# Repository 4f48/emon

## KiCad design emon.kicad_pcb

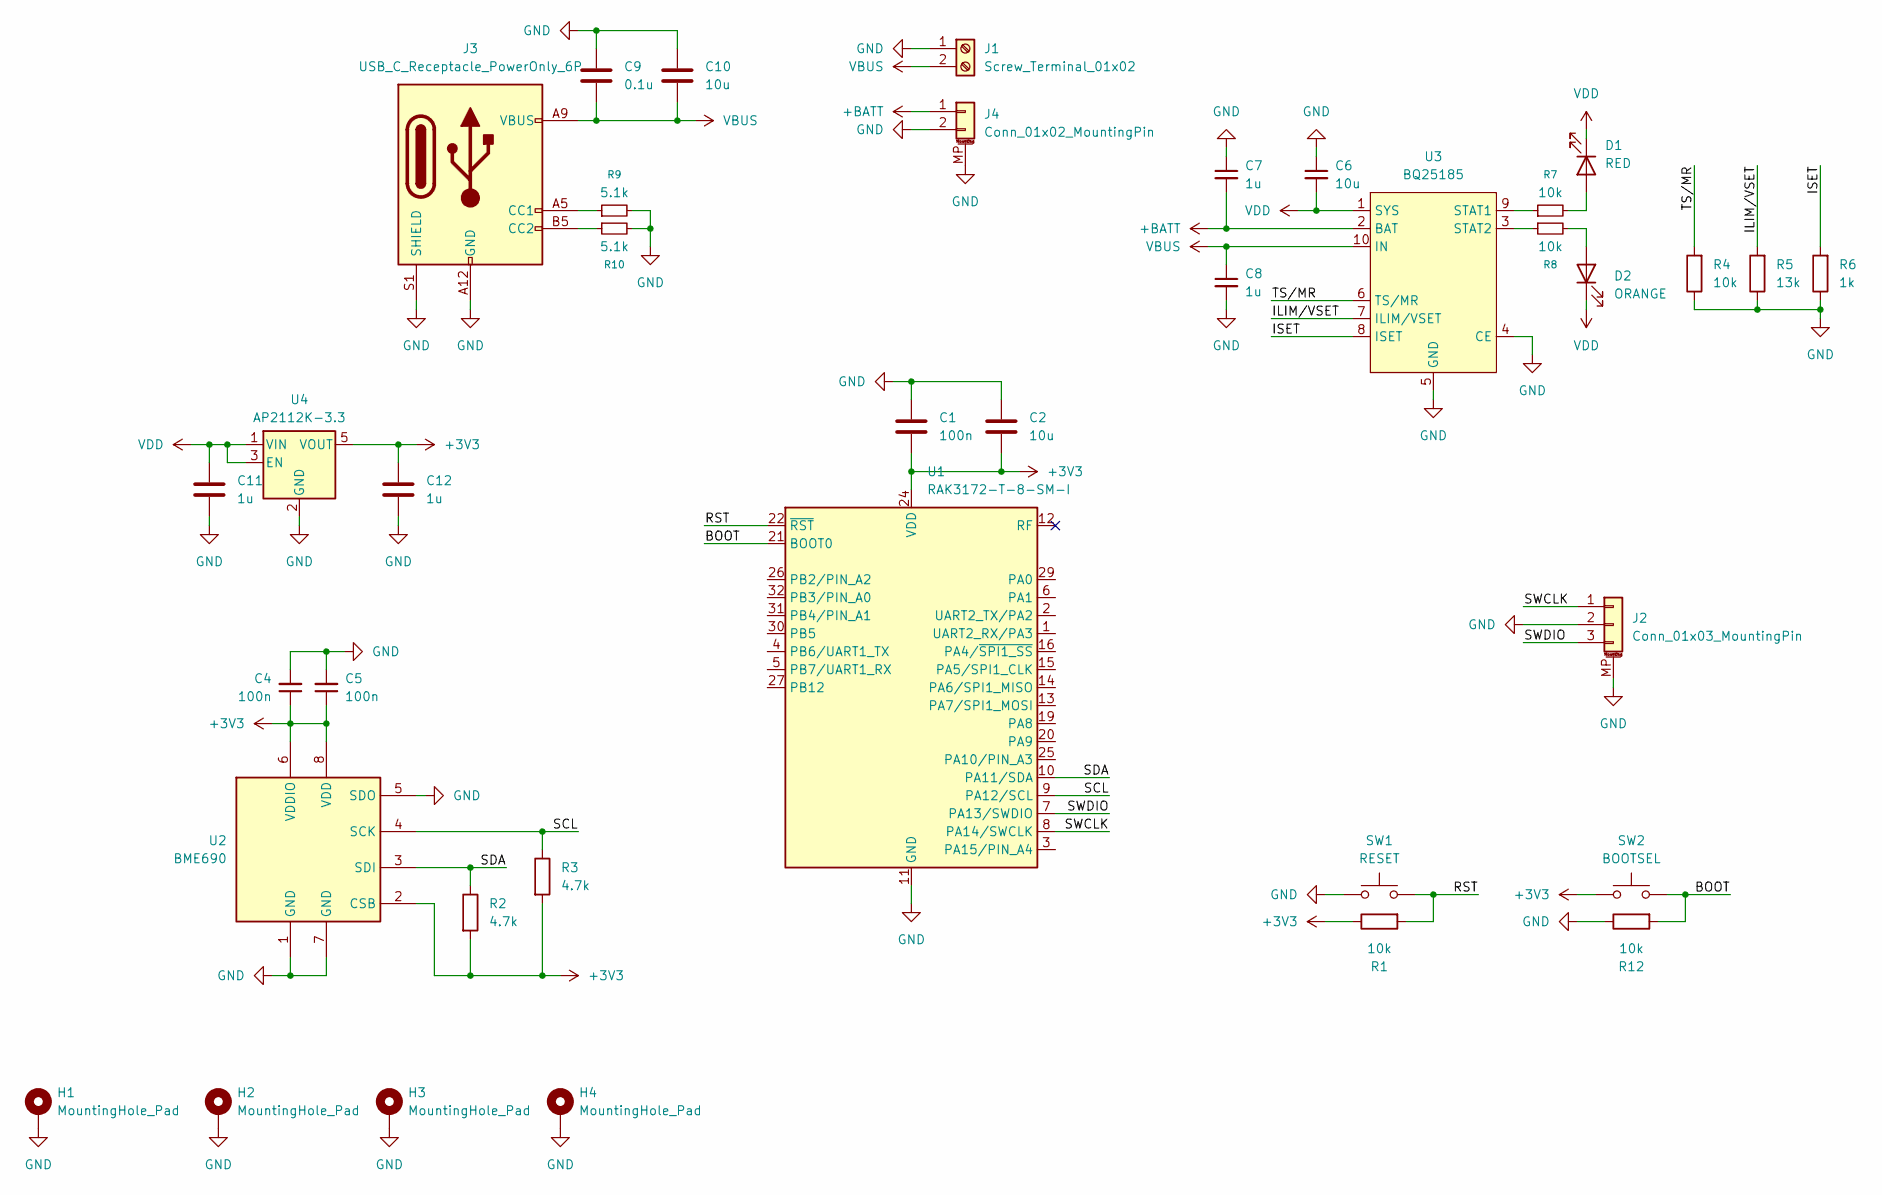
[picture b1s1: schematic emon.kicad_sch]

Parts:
C1, C4, C5: 100n; C_0201_0603Metric
C2, C10: 10u; C_0603_1608Metric
C6: 10u; C_0402_1005Metric
C7, C8: 1u; C_0402_1005Metric
C9: 0.1u; C_0201_0603Metric
C11, C12: 1u; C_0603_1608Metric_Pad1.08x0.95mm_HandSolder; MPN EMK107B7105KA-T
D1: RED; LED_0603_1608Metric; MPN LTST-C191KRKT
D2: ORANGE; LED_0603_1608Metric; MPN LTST-C191KFKT
H1, H2, H3, H4: MountingHole_Pad; MountingHole_2.7mm_M2.5_ISO14580_Pad
J1: Screw_Terminal_01x02; TerminalBlock_MetzConnect_Type059_RT06302HBWC_1x02_P3.50mm_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
J2: Conn_01x03_MountingPin; JST_SH_BM03B-SRSS-TB_1x03-1MP_P1.00mm_Vertical
J3: USB_C_Receptacle_PowerOnly_6P; USB_C_Receptacle_GCT_USB4125-xx-x_6P_TopMnt_Horizontal; MPN USB4125-GF-A
J4: Conn_01x02_MountingPin; JST_PH_S2B-PH-SM4-TB_1x02-1MP_P2.00mm_Horizontal
R1, R4, R7, R8, R12: 10k; R_0201_0603Metric
R2, R3: 4.7k; R_0201_0603Metric
R5: 13k; R_0201_0603Metric
R6: 1k; R_0201_0603Metric
R9, R10: 5.1k; R_0201_0603Metric
SW1: RESET; SW_SPST_PTS810
SW2: BOOTSEL; SW_SPST_PTS810
U1: RAK3172-T-8-SM-I; RAK3172
U2: BME690; Bosch_LGA-8_3x3mm_P0.8mm_ClockwisePinNumbering
U3: BQ25185; Texas_DLH0010A_WSON-10-1EP_2.2x2mm_P0.4mm_EP0.9x1.5mm_Therm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
U4: AP2112K-3.3; SOT-23-5_HandSoldering; MPN AP2112K-3.3TRG1

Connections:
+3V3: C1.2, C2.2, C4.1, C5.1, C12.1, R1.1, R2.2, R3.2, SW2.1, U1.24 (VDD), U2.2 (CSB), U2.6 (VDDIO), U2.8 (VDD), U4.5 (VOUT)
+BATT: C7.2, J4.1, U3.2 (BAT)
/BOOT: R12.2, SW2.2, U1.21 (BOOT0)
/ILIM/VSET: R5.2, U3.7 (ILIM/VSET)
/ISET: R6.2, U3.8 (ISET)
/RST: R1.2, SW1.2, U1.22 (~RST)
/SCL: R3.1, U1.9 (PA12/SCL), U2.4 (SCK)
/SDA: R2.1, U1.10 (PA11/SDA), U2.3 (SDI)
/SWCLK: J2.1, U1.8 (PA14/SWCLK)
/SWDIO: J2.3, U1.7 (PA13/SWDIO)
/TS/MR: R4.2, U3.6 (TS/MR)
GND: C1.1, C2.1, C4.2, C5.2, C6.1, C7.1, C8.2, C9.1, C10.1, C11.2, C12.2, H1.1 (1_1), H2.1 (1_1), H3.1 (1_1), H4.1 (1_1), J1.1, J2.2, J2.MP (MountPin), J3.A12 (GND), J3.B12 (GND), J3.S1 (SHIELD), J4.2, J4.MP (MountPin), R4.1, R5.1, R6.1, R9.2, R10.2, R12.1, SW1.1, U1.11 (GND), U1.17 (GND), U1.18 (GND), U1.23 (GND), U1.28 (GND), U2.1 (GND), U2.5 (SDO), U2.7 (GND), U3.4 (CE), U3.5 (GND), U3.11 (GND), U4.2 (GND)
unnamed: D1.2 (A), R7.2
unnamed: D2.2 (A), R8.2
unnamed: J3.A5 (CC1), R9.1
unnamed: J3.B5 (CC2), R10.1
unnamed: R7.1, U3.9 (STAT1)
unnamed: R8.1, U3.3 (STAT2)
VBUS: C8.1, C9.2, C10.2, J1.2, J3.A9 (VBUS), J3.B9 (VBUS), U3.10 (IN)
VDD: C6.2, C11.1, D1.1 (K), D2.1 (K), U3.1 (SYS), U4.1 (VIN), U4.3 (EN)

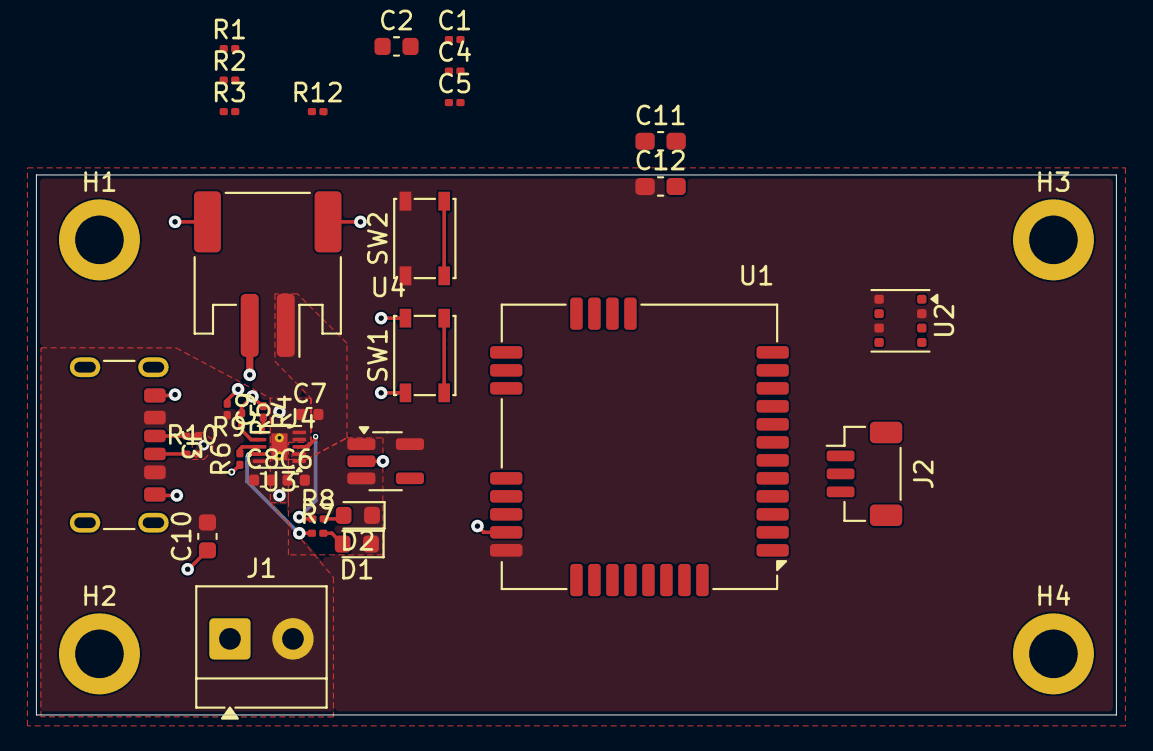
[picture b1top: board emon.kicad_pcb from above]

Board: 2 copper layers, 60.0 x 30.0 mm, 38 parts (0 on the bottom side), 20 nets.

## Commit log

2026-05-03 upload current
2026-05-03 finish schematic, start layout
2026-05-05 layout progress
